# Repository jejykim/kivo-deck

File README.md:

# Kivo Deck

Kivo Lab에서 직접 만든 DIY 스트림덱이에요. 4인치 터치 화면 위에 투명 아크릴 키 15개를 얹고, 노브 2개와 페이더 2개를 달았어요.

## 다운로드

| 파일 | 링크 |
|---|---|
| Windows 설치 파일 (.exe) | [Kivo.Deck_0.3.4_x64-setup.exe](https://github.com/jejykim/kivo-deck/releases/download/v0.3.4/Kivo.Deck_0.3.4_x64-setup.exe) |
| Mac 설치 파일 (.dmg, Intel·Apple 칩 공용) | [Kivo.Deck_0.3.4_universal.dmg](https://github.com/jejykim/kivo-deck/releases/download/v0.3.4/Kivo.Deck_0.3.4_universal.dmg) |
| 보드 펌웨어 (.bin) | [kivo-deck-firmware-0.3.4.bin](https://github.com/jejykim/kivo-deck/releases/download/v0.3.4/kivo-deck-firmware-0.3.4.bin) |

다른 버전은 [릴리스 페이지](https://github.com/jejykim/kivo-deck/releases/latest)에서 받을 수 있어요.

## 설치

**Windows**: `.exe`를 실행하세요. 설치 파일에 회사 인증서 서명이 없어서 "Windows의 PC 보호" 창이 뜰 수 있어요. 그때는 **추가 정보 → 실행**을 누르면 돼요.

**Mac**: `.dmg`를 열어 앱을 응용 프로그램 폴더로 옮기세요. 개발자 인증이 없어서 처음에는 그냥 열리지 않을 수 있어요. 그때는 앱을 **우클릭 → 열기**로 여세요. 그래도 막히면 시스템 설정 → 개인정보 보호 및 보안에서 허용하세요.

앱을 설치한 뒤에는 새 버전이 나오면 앱 상단의 아이콘으로 알려 줘요.

## 사용법

1. 보드를 USB-C로 PC에 연결해요. 앱이 보드를 자동으로 찾아요.
2. 처음 쓰는 보드라면 화면 안내대로 **노브 1을 누르고**, 화살표 끝을 차례로 눌러 터치를 보정해요.
3. 오른쪽 기능 목록에서 원하는 기능을 끌어다 키·노브·페이더에 놓아요.
4. **보드에 적용**을 누르면 설정이 보드에 저장돼요. 보드가 직접 실행하는 기능은 앱을 꺼도 동작해요.
5. 키가 잘 안 눌리거나 옆 키가 같이 눌리면 **설정 → 터치 조절**에서 압력을 보며 맞춰요. 일부 키만 어긋나면 그 안의 **키별 위치 보정**으로 키마다 위치를 재요. 값은 보드마다 따로 저장돼요.

## 할 수 있는 일

- **키**: 누르기, 길게 누르기, 두 번 누르기, 토글. 글자·이미지·GIF, 영상을 GIF로 변환, 여러 칸에 걸친 이미지
- **노브·페이더**: 볼륨(시스템·마이크·앱별)과 단축키. 노브는 누른 채 돌리기도 돼요
- **동작**: 단축키, 문자 입력, 매크로, 미디어 키, 사운드보드, 앱·파일 열기, 페이지와 폴더 이동, 소리 출력 장치 바꾸기(Windows)
- **실시간 키**: 시계, 날짜, CPU, 메모리, GPU, 스톱워치
- **프로그램별 기능**: Photoshop, Premiere Pro, Figma, OBS, Claude, ChatGPT, DeepSeek 하네스, Steam, Ollama, VS Code, Antigravity, ComfyUI
- **편의 기능**: 프로그램에 따라 페이지 자동 전환, OS별 프리셋 3칸, 프리셋 내보내기·가져오기, 화면 보호, 로그인 시 자동 실행

## 보드 펌웨어

**이미 0.3.0 이상이 들어 있는 보드**는 앱의 **설정 → 펌웨어 업데이트**에서 최신 릴리스나 내려받은 `.bin` 파일로 바로 업데이트할 수 있어요. 버튼을 누를 필요가 없고, 터치 보정 값과 키 설정도 그대로 남아요. 새 펌웨어가 정상적으로 켜지지 않으면 보드가 이전 버전으로 스스로 돌아가요.

**새 보드나 0.3.0보다 오래된 보드**는 USB로 한 번 직접 올려야 해요.

1. ESP32의 **BOOT**를 누른 채 **RST**를 눌렀다 떼고, BOOT도 떼요.
2. [PlatformIO](https://platformio.org/)를 설치한 뒤 `firmware` 폴더에서 아래 명령을 실행해요.

```powershell
pio run -t upload
```

릴리스 펌웨어는 페이더가 달려 있고 위로 올릴수록 값이 커지도록 맞춰져 있어요. 페이더가 없는 보드는 `firmware/src/config.h`의 `FADERS_INSTALLED`를 `0`으로, 방향이 반대인 보드는 `FADER1_INVERT`·`FADER2_INVERT`를 바꿔 직접 빌드해 주세요.

## 하드웨어

- ESP32-S3-DevKitC-1 N16R8
- 4인치 480×320 ST7796S 화면 + XPT2046 터치
- EC11 엔코더 2개, 60 mm 페이더 2개
- 투명 아크릴 키 15개, 뒷면 USB-C

PCB 거버, 3D 출력 파일, 아크릴 도면은 [`hardware/`](hardware/)에 있고 치수와 핀 배정은 [`docs/hardware.md`](docs/hardware.md)에 있어요.

## 직접 빌드하기

```powershell
# 앱 (Node.js, Rust 필요)
cd app
npm install
npm run tauri dev

# 펌웨어 (PlatformIO 필요)
cd firmware
pio run
```

## 폴더

- `firmware/` — ESP32-S3 펌웨어 (PlatformIO)
- `app/` — PC 앱 (Tauri 2 + React)
- `docs/` — 하드웨어, 기기↔앱 통신 규격, 개발 순서
- `hardware/` — PCB, 3D 출력, 아크릴 제작 파일

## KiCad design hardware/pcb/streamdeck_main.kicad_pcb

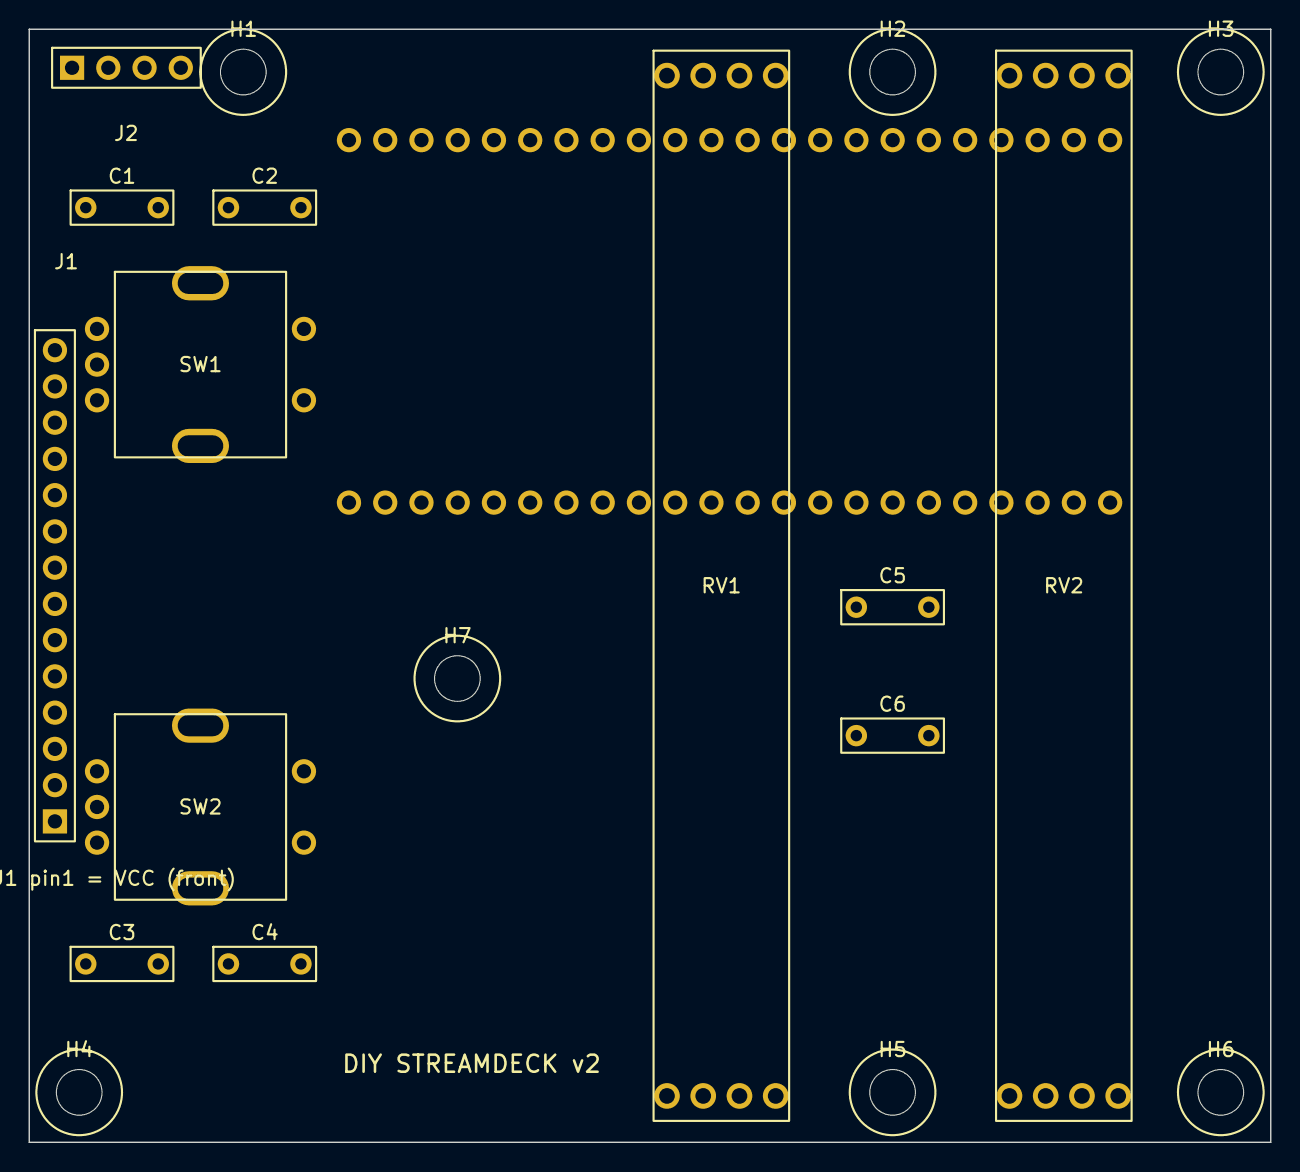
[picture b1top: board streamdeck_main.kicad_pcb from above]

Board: 2 copper layers, 87.0 x 78.0 mm, 20 parts (0 on the bottom side), 21 nets, no tracks yet.

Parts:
C1: 100nF (optional); C1
C2: 100nF (optional); C2
C3: 100nF (optional); C3
C4: 100nF (optional); C4
C5: 100nF (optional); C5
C6: 100nF (optional); C6
H1: M3 mounting hole (standoff to top plate); H1
H2: M3 mounting hole (standoff to top plate); H2
H3: M3 mounting hole (standoff to top plate); H3
H4: M3 mounting hole (standoff to top plate); H4
H5: M3 mounting hole (standoff to top plate); H5
H6: M3 mounting hole (standoff to top plate); H6
H7: M3 mounting hole (standoff to top plate); H7
J1: Wire pads to LCD MSP4021 header, 1:1 (pin1 VCC to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; J1
J2: Wire pads to USB-C breakout (back wall): 5V GND D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; J2
RV1: Slide pot dual B10K, 60mm travel, 75mm body; RV1
RV2: Slide pot dual B10K, 60mm travel, 75mm body; RV2
SW1: EC11 encoder w/ switch, 20mm half shaft; SW1
SW2: EC11 encoder w/ switch, 20mm half shaft; SW2
U1: ESP32-S3-DevKitC N16R8 (socket, bottom); U1

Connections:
+3V3: J1.1, J1.8, RV1.6, RV2.6, U1.L1, U1.L2
+5V: J2.5V, U1.L21
ENC1_A: C1.1, SW1.A, U1.L4
ENC1_B: C2.1, SW1.B, U1.L5
ENC1_SW: SW1.S1, U1.L6
ENC2_A: C3.1, SW2.A, U1.L10
ENC2_B: C4.1, SW2.B, U1.L11
ENC2_SW: SW2.S1, U1.R18
FADER1: C5.1, RV1.2, U1.R4
FADER2: C6.1, RV2.2, U1.R5
GND: C1.2, C2.2, C3.2, C4.2, C5.2, C6.2, J1.2, J2.GND, RV1.1, RV2.1, SW1.C, SW1.MP, SW1.S2, SW2.C, SW2.MP, SW2.S2, U1.L22, U1.R1, U1.R21, U1.R22
LCD_CS: J1.3, U1.L16
LCD_DC: J1.5, U1.L15
LCD_RST: J1.4, U1.L12
SPI_MISO: J1.13, U1.L19
SPI_MOSI: J1.6, J1.12, U1.L17
SPI_SCK: J1.7, J1.10, U1.L18
TP_CS: J1.11, U1.L9
TP_IRQ: J1.14, U1.L8
USB_DM: J2.D-, U1.R20
USB_DP: J2.D+, U1.R19

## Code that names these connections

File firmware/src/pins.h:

// Pin map — matches the main PCB v2 (see docs/hardware.md). Signal pins can be changed here
// without a new PCB; power pins (3V3/GND/5V) cannot.
#pragma once

// LCD MSP4021 (ST7796S) + XPT2046 resistive touch share one SPI bus
#define PIN_SPI_SCK   12
#define PIN_SPI_MOSI  11
#define PIN_SPI_MISO  13   // touch T_DO only (LCD SDO is not connected)
#define PIN_LCD_CS    10
#define PIN_LCD_DC     9
#define PIN_LCD_RST    8
#define PIN_TP_CS     16
#define PIN_TP_IRQ    15   // low while touched
// LCD backlight (LED) is tied to 3V3 on the PCB: always on.

// EC11 encoders (C pin and the switch's other leg go to GND -> use internal pull-ups)
#define PIN_ENC1_A     4
#define PIN_ENC1_B     5
#define PIN_ENC1_SW    6
#define PIN_ENC2_A    17
#define PIN_ENC2_B    18
#define PIN_ENC2_SW   21

// Faders (wiper -> ADC1). Track ends: 3V3 and GND.
#define PIN_FADER1     1
#define PIN_FADER2     2

// USB D-/D+ = GPIO19/GPIO20 (native USB, wired to the rear USB-C board through J2)
// Spare: GPIO38, 14, 39, 40, 41, 42, 47

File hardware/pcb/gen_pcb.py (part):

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front_row = ["3V3", "3V3", "RST", "4", "5", "6", "7", "15", "16", "17", "18", "8", "3", "46",
             "9", "10", "11", "12", "13", "14", "5V", "G"]
front_row[-1] = "GND"
GPIO_NET = {"10": "LCD_CS", "9": "LCD_DC", "8": "LCD_RST", "11": "SPI_MOSI", "12": "SPI_SCK",
            "13": "SPI_MISO", "16": "TP_CS", "15": "TP_IRQ",
            "4": "ENC1_A", "5": "ENC1_B", "6": "ENC1_SW",
            "17": "ENC2_A", "18": "ENC2_B", "21": "ENC2_SW",
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
# ---------------------------------------------------------------- LCD MSP4021 (rotated 180 deg, header on the right)
LCD = (7.5, 14.63, 115.5, 76.37)
LCD_PINS = ["+3V3", "GND", "LCD_CS", "LCD_RST", "LCD_DC", "SPI_MOSI", "SPI_SCK",
            "+3V3",          # 8 LED backlight -> always on
            "",              # 9 SDO (LCD MISO) not connected
            "SPI_SCK", "TP_CS", "SPI_MOSI", "SPI_MISO", "TP_IRQ"]
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   outline=("rect", lcd_x - 1.4, lcd_y0 - 1.4, lcd_x + 1.4, lcd_y0 + 13 * 2.54 + 1.4), label_xy=(lcd_x + 0.8, lcd_y0 - 6.2))

# ---------------------------------------------------------------- J2: wire pads to the USB-C breakout on the back wall
USB_PINS = [("5V", "+5V"), ("GND", "GND"), ("D-", "USB_DM"), ("D+", "USB_DP")]
usb_x0, usb_y = 119.0, 9.2
fp("J2", "Wire pads to USB-C breakout (back wall): 5V GND D- D+",
   [thp(nm, usb_x0 + k * 2.54, usb_y, net, d=1.0, s=1.7, shape="rect" if k == 0 else "circle")
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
